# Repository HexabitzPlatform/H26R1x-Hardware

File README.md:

# H26R1x-Hardware
Hexabitz High-precision Load Cell and Thermocouple Interface Module Hardware Design

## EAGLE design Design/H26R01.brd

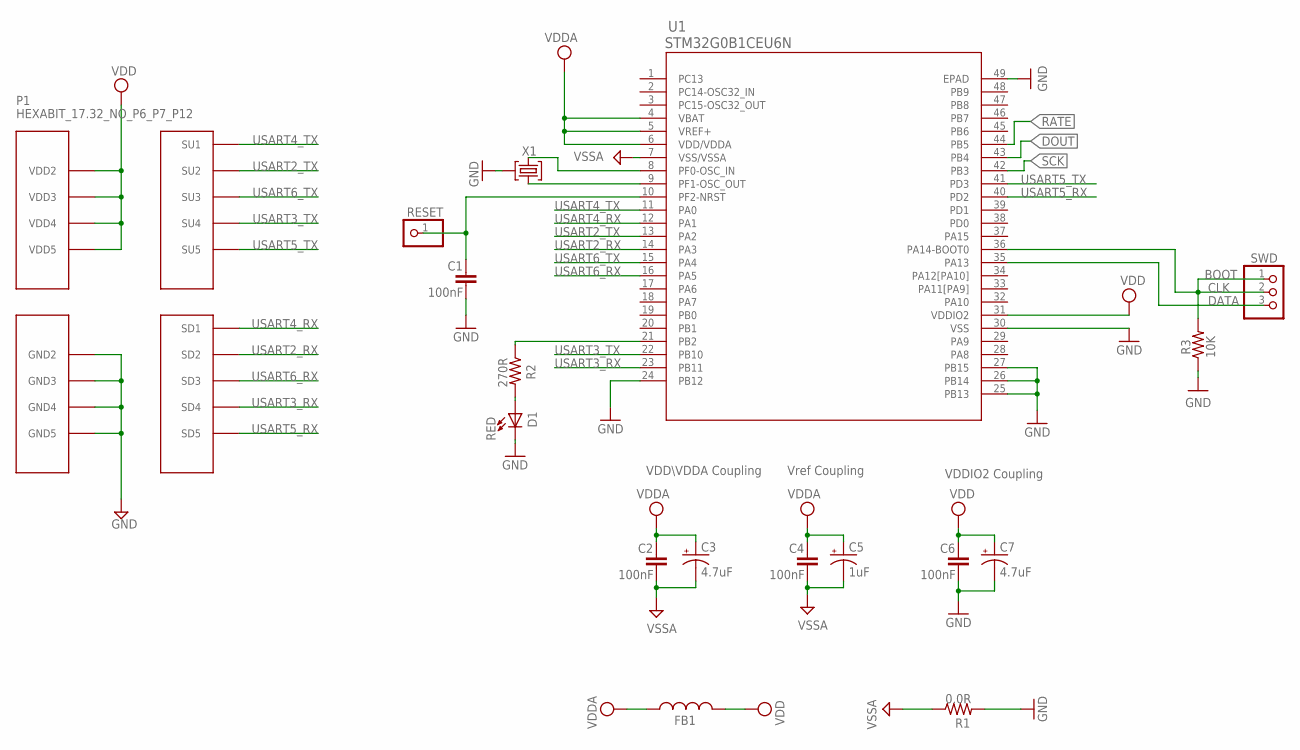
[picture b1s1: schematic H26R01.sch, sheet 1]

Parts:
C1, C2, C4, C6: 100nF; C-0603
C3, C7: 4.7uF; C-0805-POL
C5: 1uF; C-0805-POL
D1: RED; VLMS1300-GS08; MPN VLMS1300-GS08
FB1: FB-0603
P1: HEXABIT_17.32_NO_P6_P7_P12
R1: 0.0R; R-0603
R2: 270R; R-0603
R3: 10K; R-0603
RESET: R; 1X01
SWD: PINHD-1X3; 1X03
U1: STM32G0B1CEU6N; HEXABITZ_ICS_QFN_B1CEU6_STM-L
X1: XTALL_CSTCE8M00G52

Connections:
CLK: R3.2, SWD.1, SWD.2, U1.36 (PA14-BOOT0)
DATA: SWD.3, U1.35 (PA13)
DOUT: U1.43 (PB4); also elsewhere on the board
GND: C1.2, C6.2, C7.2 (-), D1.C, P1.PAD_PD8 (GND2), P1.PAD_PD9 (GND3), P1.PAD_PD10 (GND4), P1.PAD_PD11 (GND5), R1.2, R3.1, U1.24 (PB12), U1.25 (PB13), U1.26 (PB14), U1.27 (PB15), U1.30 (VSS), U1.49 (EPAD), X1.P$2 (2); also elsewhere on the board
unnamed: D1.A, R2.2
unnamed: R2.1, U1.21 (PB2)
unnamed: U1.9 (PF1-OSC_OUT), X1.P$1 (1)
unnamed: U1.8 (PF0-OSC_IN), X1.P$3 (3)
unnamed: C1.1, RESET.1, U1.10 (PF2-NRST)
RATE: U1.44 (PB5); also elsewhere on the board
SCK: U1.42 (PB3); also elsewhere on the board
USART2_RX: P1.PAD_PD2 (SD2), U1.14 (PA3)
USART2_TX: P1.PAD_PU2 (SU2), U1.13 (PA2)
USART3_RX: P1.PAD_PD4 (SD4), U1.23 (PB11)
USART3_TX: P1.PAD_PU4 (SU4), U1.22 (PB10)
USART4_RX: P1.PAD_PD1 (SD1), U1.12 (PA1)
USART4_TX: P1.PAD_PU1 (SU1), U1.11 (PA0)
USART5_RX: P1.PAD_PD5 (SD5), U1.40 (PD2)
USART5_TX: P1.PAD_PU5 (SU5), U1.41 (PD3)
USART6_RX: P1.PAD_PD3 (SD3), U1.16 (PA5)
USART6_TX: P1.PAD_PU3 (SU3), U1.15 (PA4)
VDD: C6.1, C7.1 (+), FB1.2, P1.PAD_PU8 (VDD2), P1.PAD_PU9 (VDD3), P1.PAD_PU10 (VDD4), P1.PAD_PU11 (VDD5), U1.31 (VDDIO2); also elsewhere on the board
VDDA: C2.1, C3.1 (+), C4.1, C5.1 (+), FB1.1, U1.4 (VBAT), U1.5 (VREF+), U1.6 (VDD/VDDA); also elsewhere on the board
VSSA: C2.2, C3.2 (-), C4.2, C5.2 (-), R1.1, U1.7 (VSS/VSSA); also elsewhere on the board

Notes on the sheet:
Vref Coupling
VDDIO2 Coupling
VDD\VDDA Coupling
BOOT

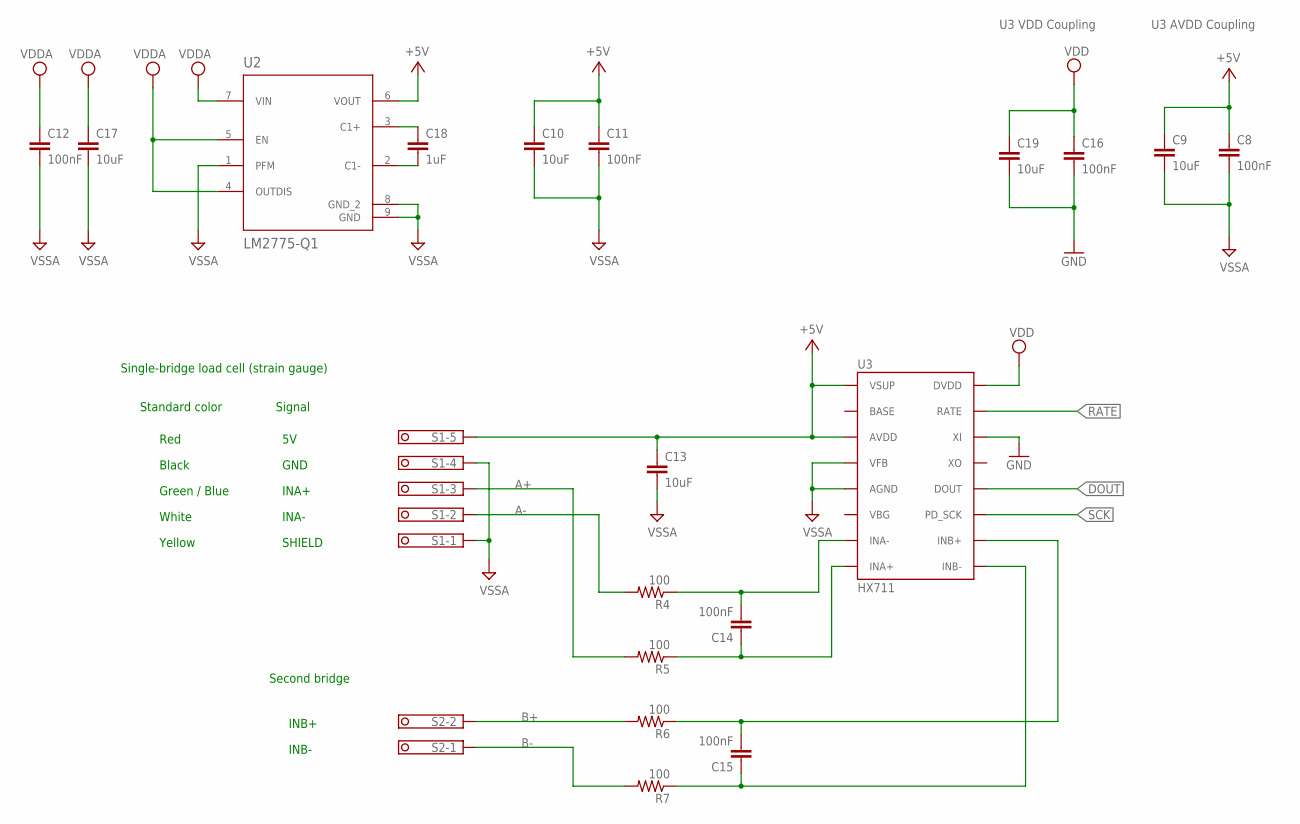
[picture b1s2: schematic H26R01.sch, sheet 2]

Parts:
C8, C11, C12, C16: 100nF; C-0603; TOLERANCE 10%; VOLTAGE_RATING 10V; MPN C0603C104K8RACTU
C9, C10, C13, C17, C19: 10uF; C-0603; TOLERANCE 10%; VOLTAGE_RATING 10V; MPN GRM188R61A106KE69D
C14, C15: 100nF; C-0603; TOLERANCE 10V; VOLTAGE_RATING 10%; MPN C0603C104K8RACTU
C18: 1uF; C-0603; TOLERANCE 10%; VOLTAGE_RATING 10V; MPN GRM188R61A105KA61J
R4, R5, R6, R7: 100; R-0603; TOLERANCE 5%; MPN RC0603JR-07100RL
S1: CON-PHOENIX-350_1751277; MPN 1984646
S2: CON-PHOENIX-350_1751248; MPN 1984617
U2: LM2775-Q1; DSG0008A
U3: HX711; HX711_SO16; MPN HX711

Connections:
+5V: C8.1, C9.1, C10.1, C11.1, C13.1, S1.5, U2.6 (VOUT), U3.1 (VSUP), U3.3 (AVDD)
A+: R5.2, S1.3
A-: R4.2, S1.2
B+: R6.2, S2.2
B-: R7.2, S2.1
DOUT: U3.12 (DOUT); also elsewhere on the board
GND: C16.2, C19.2, U3.14 (XI); also elsewhere on the board
INA+: C14.1, R5.1, U3.8 (INA+)
INA-: C14.2, R4.1, U3.7 (INA-)
INB+: C15.2, R6.1, U3.10 (INB+)
INB-: C15.1, R7.1, U3.9 (INB-)
unnamed: C18.1, U2.3 (C1+)
unnamed: C18.2, U2.2 (C1-)
RATE: U3.15 (RATE); also elsewhere on the board
SCK: U3.11 (PD_SCK); also elsewhere on the board
VDD: C16.1, C19.1, U3.16 (DVDD); also elsewhere on the board
VDDA: C12.1, C17.1, U2.4 (OUTDIS), U2.5 (EN), U2.7 (VIN); also elsewhere on the board
VSSA: C8.2, C9.2, C10.2, C11.2, C12.2, C13.2, C17.2, S1.1, S1.4, U2.1 (PFM), U2.8 (GND_2), U2.9 (GND), U3.4 (VFB), U3.5 (AGND); also elsewhere on the board

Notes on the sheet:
Standard color
Red
Black
White
Green / Blue
Yellow
Single-bridge load cell (strain gauge)
GND
INA-
INA+
SHIELD
Signal
INB-
INB+
Second bridge
U3 VDD Coupling
U3 AVDD Coupling

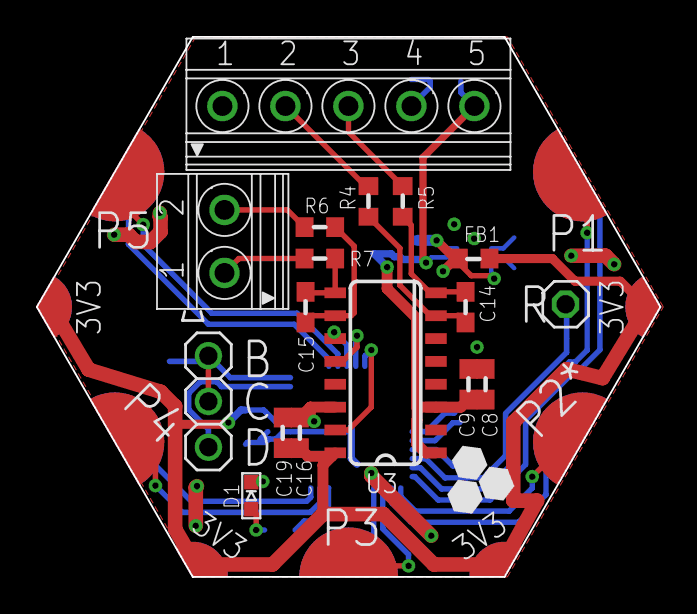
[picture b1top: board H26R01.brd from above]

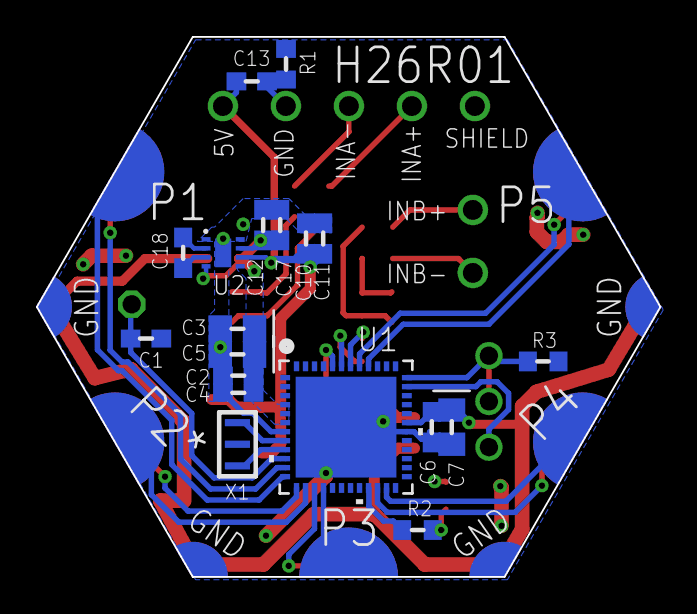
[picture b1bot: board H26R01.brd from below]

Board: 2 copper layers, 34.6 x 30.0 mm, 37 parts (19 on the bottom side), 35 nets.

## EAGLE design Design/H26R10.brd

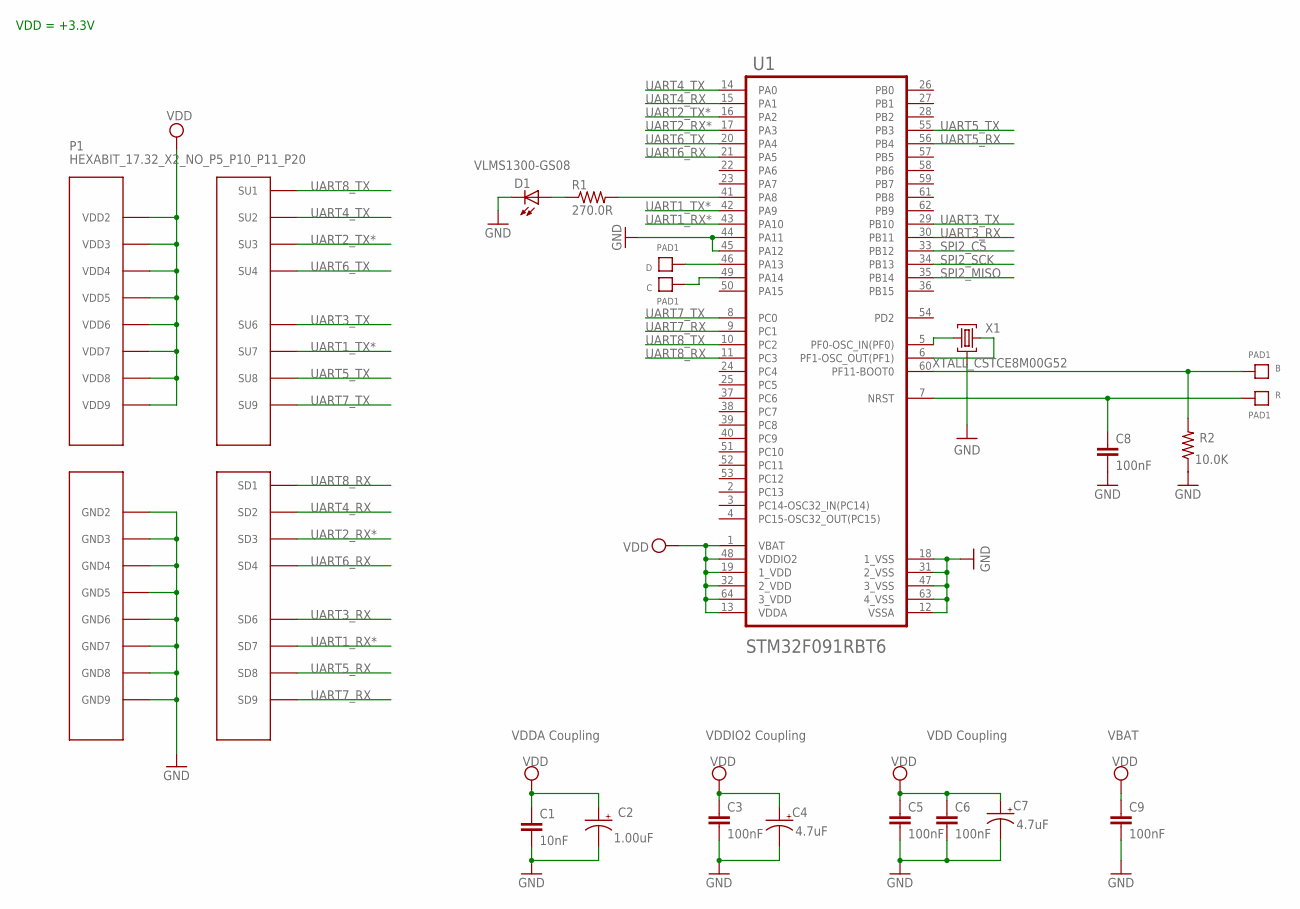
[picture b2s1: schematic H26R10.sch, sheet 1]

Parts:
B: PAD1
C: PAD1
C1: 10nF; C-0603; TOLERANCE 10%; VOLTAGE_RATING 50V; MPN C0603C103K5RACTU
C2: 1.00uF; C-0805-POL; TOLERANCE 10%; VOLTAGE_RATING 16V; MPN CC0805KKX7R7BB105
C3, C6, C8: 100nF; C-0603; TOLERANCE 10%; VOLTAGE_RATING 10V; MPN C0603C104K8RACTU
C4, C7: 4.7uF; C-0805-POL; TOLERANCE 10%; VOLTAGE_RATING 25V; MPN GRM21BC81E475KA12L
C5: 100nF; C-0603; TOLERANCE 10%; VOLTAGE_RATING 10; MPN C0603C104K8RACTU
C9: 100nF; C-0603; TOLERANCE 10V; VOLTAGE_RATING 10%; MPN C0603C104K8RACTU
D: PAD1
D1: VLMS1300-GS08; MPN VLMS1300-GS08
P1: HEXABIT_17.32_X2_NO_P5_P10_P11_P20
R: PAD1
R1: 270.0R; R-0603; TOLERANCE 1%; MPN RC0603FR-07270RL
R2: 10.0K; R-0603; TOLERANCE 5%; MPN RC0603JR-0710KL
U1: STM32F091RBT6STMICROELECTRONICS_STM32F091RBT6_0_1; STMICROELECTRONICS_STM32F091RBT6_1
X1: XTALL_CSTCE8M00G52

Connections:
B1: B.P$1, B.P$2, R2.2, U1.60 (PF11-BOOT0)
GND: C1.2, C2.2 (-), C3.2, C4.2 (-), C5.2, C6.2, C7.2 (-), C8.2, C9.2, D1.C, P1.PAD_PD12 (GND2), P1.PAD_PD13 (GND3), P1.PAD_PD14 (GND4), P1.PAD_PD15 (GND5), P1.PAD_PD16 (GND6), P1.PAD_PD17 (GND7), P1.PAD_PD18 (GND8), P1.PAD_PD19 (GND9), R2.1, U1.12 (VSSA), U1.18 (1_VSS), U1.31 (2_VSS), U1.44 (PA11), U1.45 (PA12), U1.47 (3_VSS), U1.63 (4_VSS), X1.P$2 (2); also elsewhere on the board
unnamed: R1.2, U1.41 (PA8)
unnamed: D1.A, R1.1
unnamed: U1.5 (PF0-OSC_IN(PF0)), X1.P$1 (1)
unnamed: U1.6 (PF1-OSC_OUT(PF1)), X1.P$3 (3)
unnamed: D.P$1, D.P$2, U1.46 (PA13)
unnamed: C.P$1, C.P$2, U1.49 (PA14)
R1: C8.1, R.P$1, R.P$2, U1.7 (NRST)
SPI2_CS: U1.33 (PB12); also elsewhere on the board
SPI2_MISO: U1.35 (PB14); also elsewhere on the board
SPI2_SCK: U1.34 (PB13); also elsewhere on the board
UART1_RX*: P1.PAD_PD7 (SD7), U1.43 (PA10)
UART1_TX*: P1.PAD_PU7 (SU7), U1.42 (PA9)
UART2_RX*: P1.PAD_PD3 (SD3), U1.17 (PA3)
UART2_TX*: P1.PAD_PU3 (SU3), U1.16 (PA2)
UART3_RX: P1.PAD_PD6 (SD6), U1.30 (PB11)
UART3_TX: P1.PAD_PU6 (SU6), U1.29 (PB10)
UART4_RX: P1.PAD_PD2 (SD2), U1.15 (PA1)
UART4_TX: P1.PAD_PU2 (SU2), U1.14 (PA0)
UART5_RX: P1.PAD_PD8 (SD8), U1.56 (PB4)
UART5_TX: P1.PAD_PU8 (SU8), U1.55 (PB3)
UART6_RX: P1.PAD_PD4 (SD4), U1.21 (PA5)
UART6_TX: P1.PAD_PU4 (SU4), U1.20 (PA4)
UART7_RX: P1.PAD_PD9 (SD9), U1.9 (PC1)
UART7_TX: P1.PAD_PU9 (SU9), U1.8 (PC0)
UART8_RX: P1.PAD_PD1 (SD1), U1.11 (PC3)
UART8_TX: P1.PAD_PU1 (SU1), U1.10 (PC2)
VDD: C1.1, C2.1 (+), C3.1, C4.1 (+), C5.1, C6.1, C7.1 (+), C9.1, P1.PAD_PU12 (VDD2), P1.PAD_PU13 (VDD3), P1.PAD_PU14 (VDD4), P1.PAD_PU15 (VDD5), P1.PAD_PU16 (VDD6), P1.PAD_PU17 (VDD7), P1.PAD_PU18 (VDD8), P1.PAD_PU19 (VDD9), U1.1 (VBAT), U1.13 (VDDA), U1.19 (1_VDD), U1.32 (2_VDD), U1.48 (VDDIO2), U1.64 (3_VDD); also elsewhere on the board

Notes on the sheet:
VDDA Coupling
VDDIO2 Coupling
VDD Coupling
VBAT
VDD = +3.3V

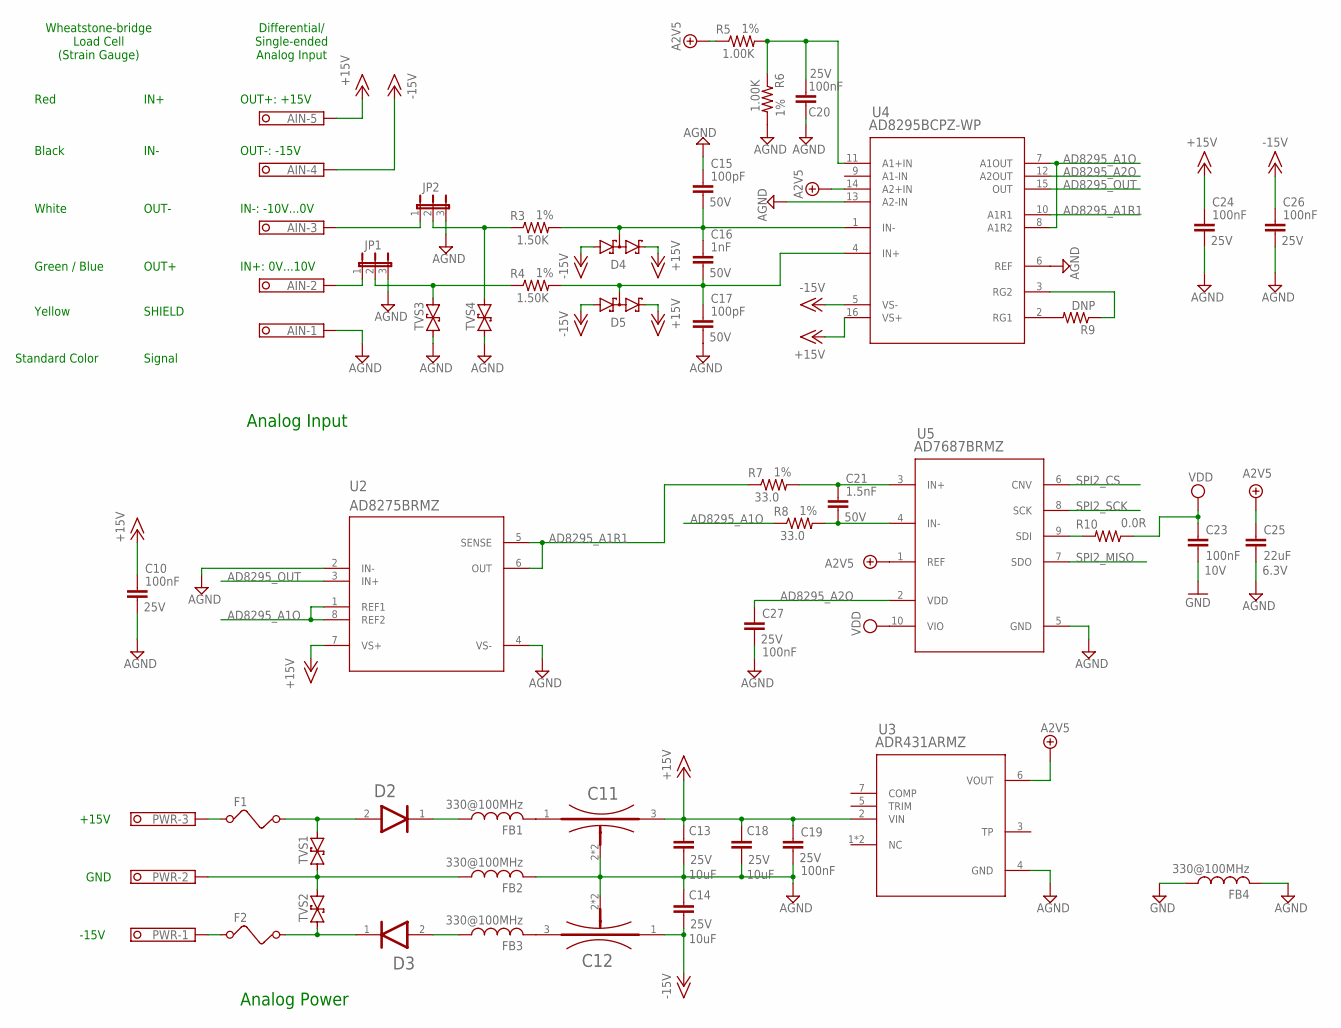
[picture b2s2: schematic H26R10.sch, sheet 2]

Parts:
AIN: CON-PHOENIX-350_1751277; MPN 1984646
C10, C24, C26, C27: 100nF; C-0603; TOLERANCE 10%; VOLTAGE_RATING 25V; MPN GRM188R71E104KA01D
C11, C12: MURATA_NFM21PC105B1A3DMURATA_NFM21PC105B1A3D_0_0; MURATA_NFM21PC105B1A3D_0
C13, C14, C18: 10uF; C1206K; VOLTAGE 25V; MPN CC1206ZKY5V8BB106
C15, C17: 100pF; C-0603; TOLERANCE 5%; VOLTAGE_RATING 50V; MPN VJ0603A101JXACW1BC
C16: 1nF; C-0603; TOLERANCE 5%; VOLTAGE_RATING 50V; MPN C0603C102J5RACTU
C19, C20: 100nF; C-0603; TOLERANCE 10%; VOLTAGE_RATING 25V; MPN C0603C104K8RACTU
C21: 1.5nF; C-0603; TOLERANCE 10%; VOLTAGE_RATING 50V; MPN GRM188R71H152KA01D
C23: 100nF; C-0603; TOLERANCE 10%; VOLTAGE_RATING 10V; MPN C0603C104K8RACTU
C25: 22uF; C1206K; VOLTAGE 6.3V; MPN C3216X5R0J226M085AC
D2, D3: DIODES_SBR2U30P1-7DIODES_SBR2U30P1-7_0_0; DIODES_SBR2U30P1-7_0
D4, D5: BAT54S; SOT23
F1, F2: NANOSMDC035F-2120; R1206
FB1, FB2, FB3, FB4: 330@100MHz; FB-0805; MPN BLM21PG331SN1D
JP1, JP2: JP2E; JP2; MPN 5-146274-3
PWR: 1751251; MPN 1751251
R3, R4: 1.50K; R-0603; TOLERANCE 1%; MPN CRCW08051K50FKEA
R5, R6: 1.00K; R-0603; TOLERANCE 1%; MPN RC0603FR-0710KL
R7, R8: 33.0; R-0603; TOLERANCE 1%; MPN CRCW060333R0FKEA
R9: DNP; R-0805
R10: 0.0R; R-0603; MPN RC0603JR-070RL
TVS1, TVS2, TVS3, TVS4: SMBJ30CA; DO214AA
U2: AD8275BRMZ; RM_8
U3: ADR431ARMZ; RM_8
U4: AD8295BCPZ-WP; CP_16_19
U5: AD7687BRMZ; RM_10

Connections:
+2.5V: C25.1, R5.1, U3.6 (VOUT), U4.14 (A2+IN), U5.1 (REF)
+15V: AIN.5, C10.1, C11.3 (OUTPUT), C13.1, C18.1, C19.1, C24.1, D4.2 (C2), D5.2 (C2), U2.7 (VS+), U3.2 (VIN), U4.16 (VS+)
-15V: AIN.4, C12.1 (INPUT), C14.2, C26.1, D4.1 (A1), D5.1 (A1), U4.5 (VS-)
AD8295_A1O: R8.1, U2.1 (REF1), U2.8 (REF2), U4.7 (A1OUT), U4.8 (A1R2)
AD8295_A1R1: R7.1, U2.5 (SENSE), U2.6 (OUT), U4.10 (A1R1)
AD8295_A2O: C27.1, U4.12 (A2OUT), U5.2 (VDD)
AD8295_OUT: U2.3 (IN+), U4.15 (OUT)
AGND: AIN.1, C10.2, C11.2 (GND), C11.2-2 (GND), C12.2 (GND), C12.2-2 (GND), C13.2, C14.1, C15.1, C17.2, C18.2, C19.2, C20.1, C24.2, C25.2, C26.2, C27.2, FB2.2, FB4.2, JP1.3, JP2.3, R6.2, TVS3.A (1), TVS4.A (1), U2.2 (IN-), U2.4 (VS-), U3.4 (GND), U4.6 (REF), U4.13 (A2-IN), U5.5 (GND)
GND: C23.2, FB4.1; also elsewhere on the board
unnamed: AIN.3, JP2.1
unnamed: AIN.2, JP1.1
unnamed: JP2.2, R3.1, TVS4.C (2)
unnamed: JP1.2, R4.1, TVS3.C (2)
unnamed: C15.2, C16.1, D4.3 (C1A2), R3.2, U4.1 (IN-)
unnamed: C16.2, C17.1, D5.3 (C1A2), R4.2, U4.4 (IN+)
unnamed: R9.2, U4.2 (RG1)
unnamed: R9.1, U4.3 (RG2)
unnamed: F1.1, PWR.3
unnamed: F2.1, PWR.1
unnamed: D2.2 (ANODE), F1.2, TVS1.C (2)
unnamed: D3.1 (CATHODE), F2.2, TVS2.A (1)
unnamed: FB2.1, PWR.2, TVS1.A (1), TVS2.C (2)
unnamed: D2.1 (CATHODE), FB1.1
unnamed: D3.2 (ANODE), FB3.1
unnamed: C11.1 (INPUT), FB1.2
unnamed: C12.3 (OUTPUT), FB3.2
unnamed: C20.2, R5.2, R6.1, U4.11 (A1+IN)
unnamed: R10.2, U5.9 (SDI)
unnamed: C21.1, R7.2, U5.3 (IN+)
unnamed: C21.2, R8.2, U5.4 (IN-)
SPI2_CS: U5.6 (CNV); also elsewhere on the board
SPI2_MISO: U5.7 (SDO); also elsewhere on the board
SPI2_SCK: U5.8 (SCK); also elsewhere on the board
VDD: C23.1, R10.1, U5.10 (VIO); also elsewhere on the board

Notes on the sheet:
Standard Color
Red
Black
White
Green / Blue
Yellow
Wheatstone-bridge Load Cell (Strain Gauge)
IN+
IN-
OUT-
OUT+
SHIELD
Signal
GND
+15V
Analog Input
Analog Power
-15V
IN+: 0V...10V
IN-: -10V...0V
Differential/ Single-ended Analog Input
OUT+: +15V
OUT-: -15V

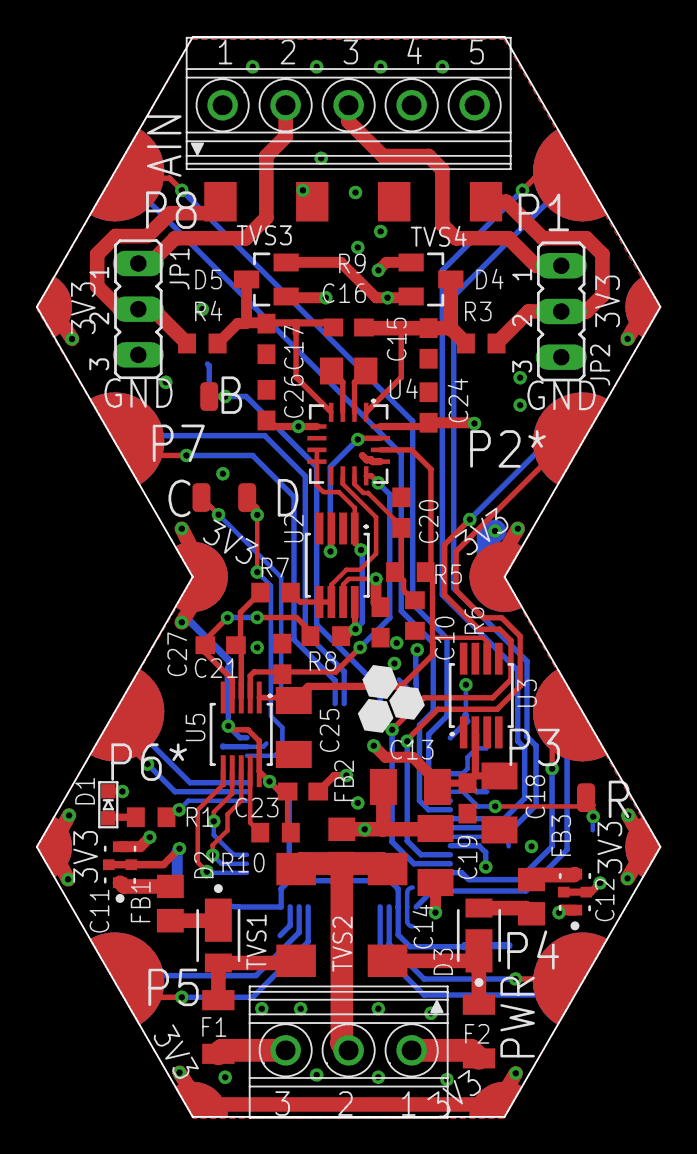
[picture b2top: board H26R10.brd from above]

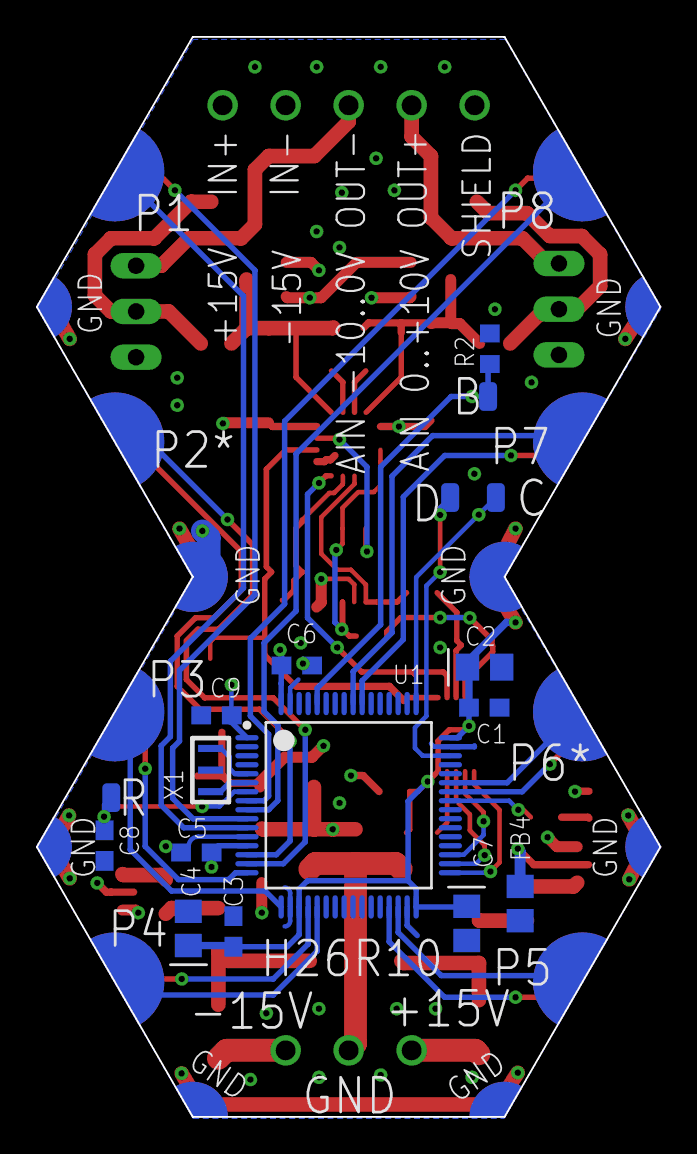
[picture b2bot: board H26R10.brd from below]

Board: 4 copper layers, 34.6 x 60.0 mm, 66 parts (13 on the bottom side), 58 nets.

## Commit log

2019-11-16 Adding template module generated from script + folders Updating schematics header Adding all AD components + analog input chain
2019-11-18 Finished analog power chain and some AD8295 connections
2019-11-21 Finished schematics. No ERC yet
2019-11-22 Renumber schematics Arrange analong path in PCB to estimate footprint Replace module connector with double hexagon Need to replace MCU with bigger package to use 8 UARTs
2019-11-25 Replace MCU with Add STM32F091RB (LQFP64) and connect UARTs
2019-12-07 Rearrange uart connections Route analog section
2019-12-07 More routing Add 2 more layers Add layer stack note
2019-12-08 Finished routing Added polygons
2019-12-08 arrange top silkscreen
2019-12-10 Finished arranging silkscreen on top and bottom and added all ports, text etc
2019-12-11 Finished routing and silkscreen.. Reviewed ERC and DRC PCB is done
2019-12-12 Generate CAM files: gerber, drill, BOM, schematics and stack Update some components attributes Ready for release 1
2019-12-16 Added pick n place files Release V0
2023-09-17 - Change the MCU to stm32g0b1ceu6n - Improve the hardware design - Do some changes in terminales naming

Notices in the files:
parts and their libraries:
HEXABITZ_ICs: COPYRIGHT: Copyright (C) 2022 Ultra Librarian. All rights reserved.
